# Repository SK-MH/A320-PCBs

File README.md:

# A320-PCBs

> [!IMPORTANT]
> This repository is still in progress.

Please wait for the documentation.
It could be found later on here.

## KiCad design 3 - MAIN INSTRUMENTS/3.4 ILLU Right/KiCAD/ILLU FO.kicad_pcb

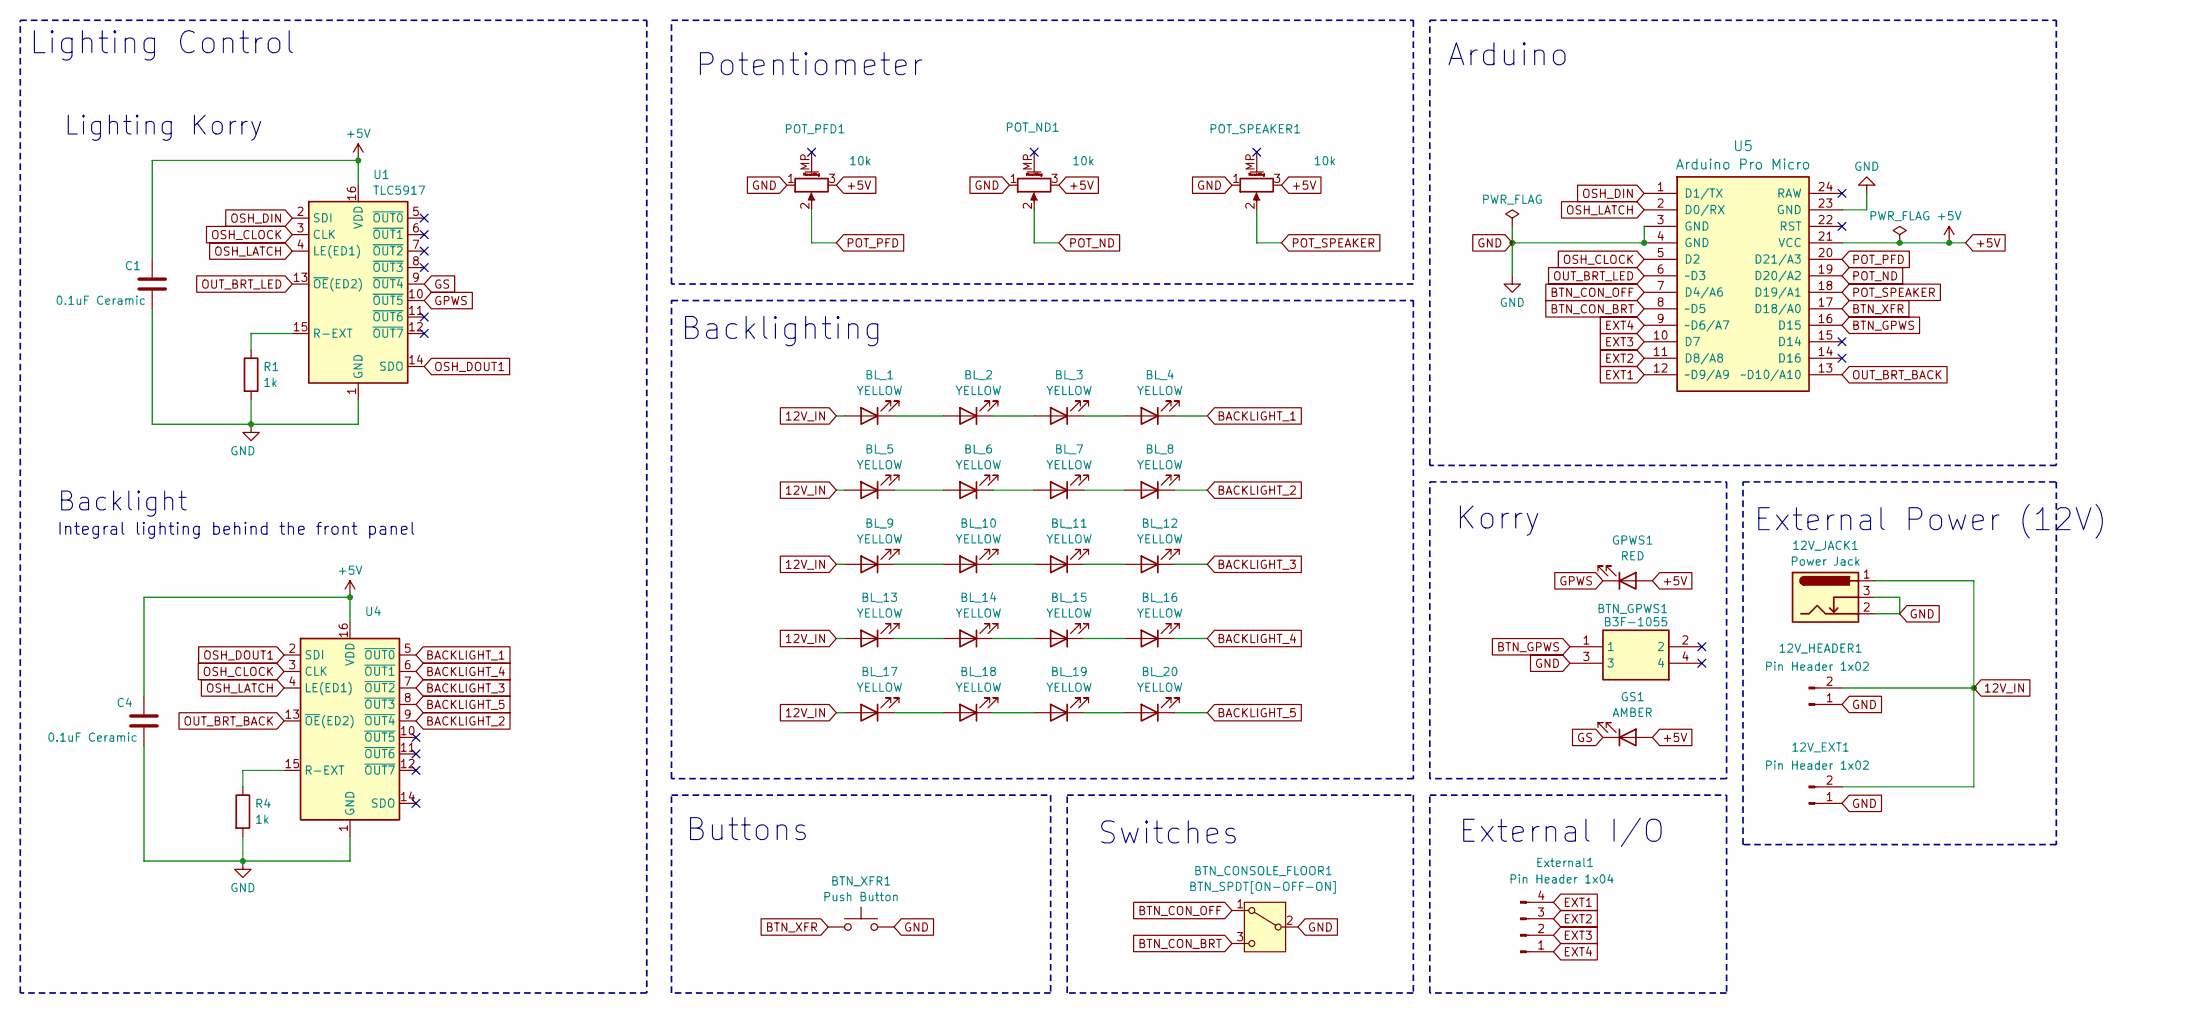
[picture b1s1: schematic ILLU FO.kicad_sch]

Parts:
12V_EXT1, 12V_HEADER1: Pin Header 1x02; JST_EH_B2B-EH-A_1x02_P2.50mm_Vertical
12V_JACK1: Power Jack; BarrelJack_Horizontal
BL_1, BL_2, BL_3, BL_4, BL_5, BL_6, BL_7, BL_8, BL_9, BL_10, BL_11, BL_12, BL_13, BL_14, BL_15, BL_16, BL_17, BL_18, BL_19, BL_20: YELLOW; LED_D3.0mm
BTN_CONSOLE_FLOOR1: BTN_SPDT[ON-OFF-ON]; T80-Z1
BTN_GPWS1: B3F-1055; B3F1000; Mouser Part Number 653-B3F-1055
BTN_XFR1: Push Button; SW-Push
C1, C4: 0.1uF Ceramic; C_Disc_D3.0mm_W1.6mm_P2.50mm
External1: Pin Header 1x04; JST_EH_B4B-EH-A_1x04_P2.50mm_Vertical
GPWS1: RED; LED_D3.0mm
GS1: AMBER; LED_D3.0mm
POT_ND1: 10k; Potentiometer_Alps_RK09K_Single_Vertical
POT_PFD1: 10k; Potentiometer_Alps_RK09K_Single_Vertical
POT_SPEAKER1: 10k; Potentiometer_Alps_RK09K_Single_Vertical
R1, R4: 1k; R_Axial_DIN0204_L3.6mm_D1.6mm_P7.62mm_Horizontal
U1, U4: TLC5917; DIP-16_W7.62mm
U5: Arduino Pro Micro; Sparkfun_Pro_Micro

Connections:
12V_IN: 12V_EXT1.2, 12V_HEADER1.2, 12V_JACK1.1, BL_1.2 (A), BL_5.2 (A), BL_9.2 (A), BL_13.2 (A), BL_17.2 (A)
+5V: C1.1, C4.1, GPWS1.2 (A), GS1.2 (A), POT_ND1.3, POT_PFD1.3, POT_SPEAKER1.3, U1.16 (VDD), U4.16 (VDD), U5.21 (VCC)
BACKLIGHT_1: BL_4.1 (K), U4.5 (~OUT0)
BACKLIGHT_2: BL_8.1 (K), U4.9 (~OUT4)
BACKLIGHT_3: BL_12.1 (K), U4.7 (~OUT2)
BACKLIGHT_4: BL_16.1 (K), U4.6 (~OUT1)
BACKLIGHT_5: BL_20.1 (K), U4.8 (~OUT3)
BTN_CON_BRT: BTN_CONSOLE_FLOOR1.3 (C), U5.8 (~D5)
BTN_CON_OFF: BTN_CONSOLE_FLOOR1.1 (A), U5.7 (D4/A6)
BTN_GPWS: BTN_GPWS1.1, U5.16 (D15)
BTN_XFR: BTN_XFR1.1, U5.17 (D18/A0)
EXT1: External1.4, U5.12 (~D9/A9)
EXT2: External1.3, U5.11 (D8/A8)
EXT3: External1.2, U5.10 (D7)
EXT4: External1.1, U5.9 (~D6/A7)
GND: 12V_EXT1.1, 12V_HEADER1.1, 12V_JACK1.2, 12V_JACK1.3, BTN_CONSOLE_FLOOR1.2 (B), BTN_GPWS1.3, BTN_XFR1.2, C1.2, C4.2, POT_ND1.1, POT_PFD1.1, POT_SPEAKER1.1, R1.2, R4.2, U1.1 (GND), U4.1 (GND), U5.3 (GND), U5.4 (GND), U5.23 (GND)
GPWS: GPWS1.1 (K), U1.10 (~OUT5)
GS: GS1.1 (K), U1.9 (~OUT4)
unnamed: BL_1.1 (K), BL_2.2 (A)
unnamed: BL_2.1 (K), BL_3.2 (A)
unnamed: BL_3.1 (K), BL_4.2 (A)
unnamed: BL_5.1 (K), BL_6.2 (A)
unnamed: BL_6.1 (K), BL_7.2 (A)
unnamed: BL_7.1 (K), BL_8.2 (A)
unnamed: BL_9.1 (K), BL_10.2 (A)
unnamed: BL_10.1 (K), BL_11.2 (A)
unnamed: BL_11.1 (K), BL_12.2 (A)
unnamed: BL_13.1 (K), BL_14.2 (A)
unnamed: BL_14.1 (K), BL_15.2 (A)
unnamed: BL_15.1 (K), BL_16.2 (A)
unnamed: BL_17.1 (K), BL_18.2 (A)
unnamed: BL_18.1 (K), BL_19.2 (A)
unnamed: BL_19.1 (K), BL_20.2 (A)
unnamed: R1.1, U1.15 (R-EXT)
unnamed: R4.1, U4.15 (R-EXT)
OSH_CLOCK: U1.3 (CLK), U4.3 (CLK), U5.5 (D2)
OSH_DIN: U1.2 (SDI), U5.1 (D1/TX)
OSH_DOUT1: U1.14 (SDO), U4.2 (SDI)
OSH_LATCH: U1.4 (LE(ED1)), U4.4 (LE(ED1)), U5.2 (D0/RX)
OUT_BRT_BACK: U4.13 (~OE(ED2)), U5.13 (~D10/A10)
OUT_BRT_LED: U1.13 (~OE(ED2)), U5.6 (~D3)
POT_ND: POT_ND1.2, U5.19 (D20/A2)
POT_PFD: POT_PFD1.2, U5.20 (D21/A3)
POT_SPEAKER: POT_SPEAKER1.2, U5.18 (D19/A1)

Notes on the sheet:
Backlighting
Arduino
Switches
External I/O
Korry
Buttons
External Power (12V)
Lighting Korry
Lighting Control
Integral lighting behind the front panel
Potentiometer
Backlight

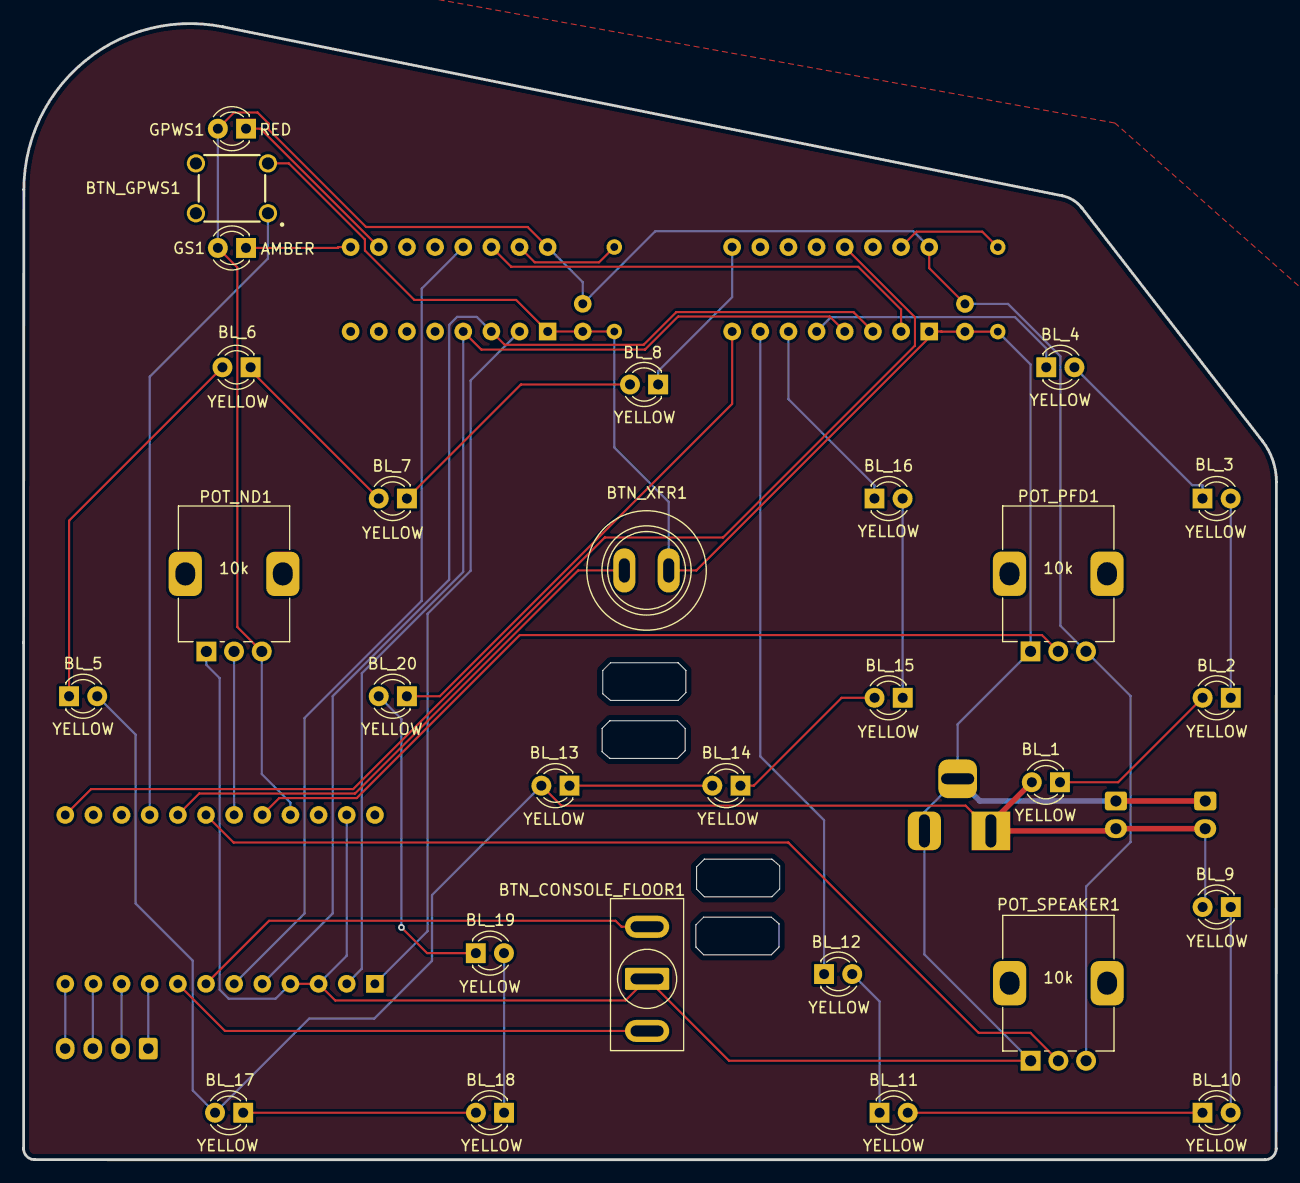
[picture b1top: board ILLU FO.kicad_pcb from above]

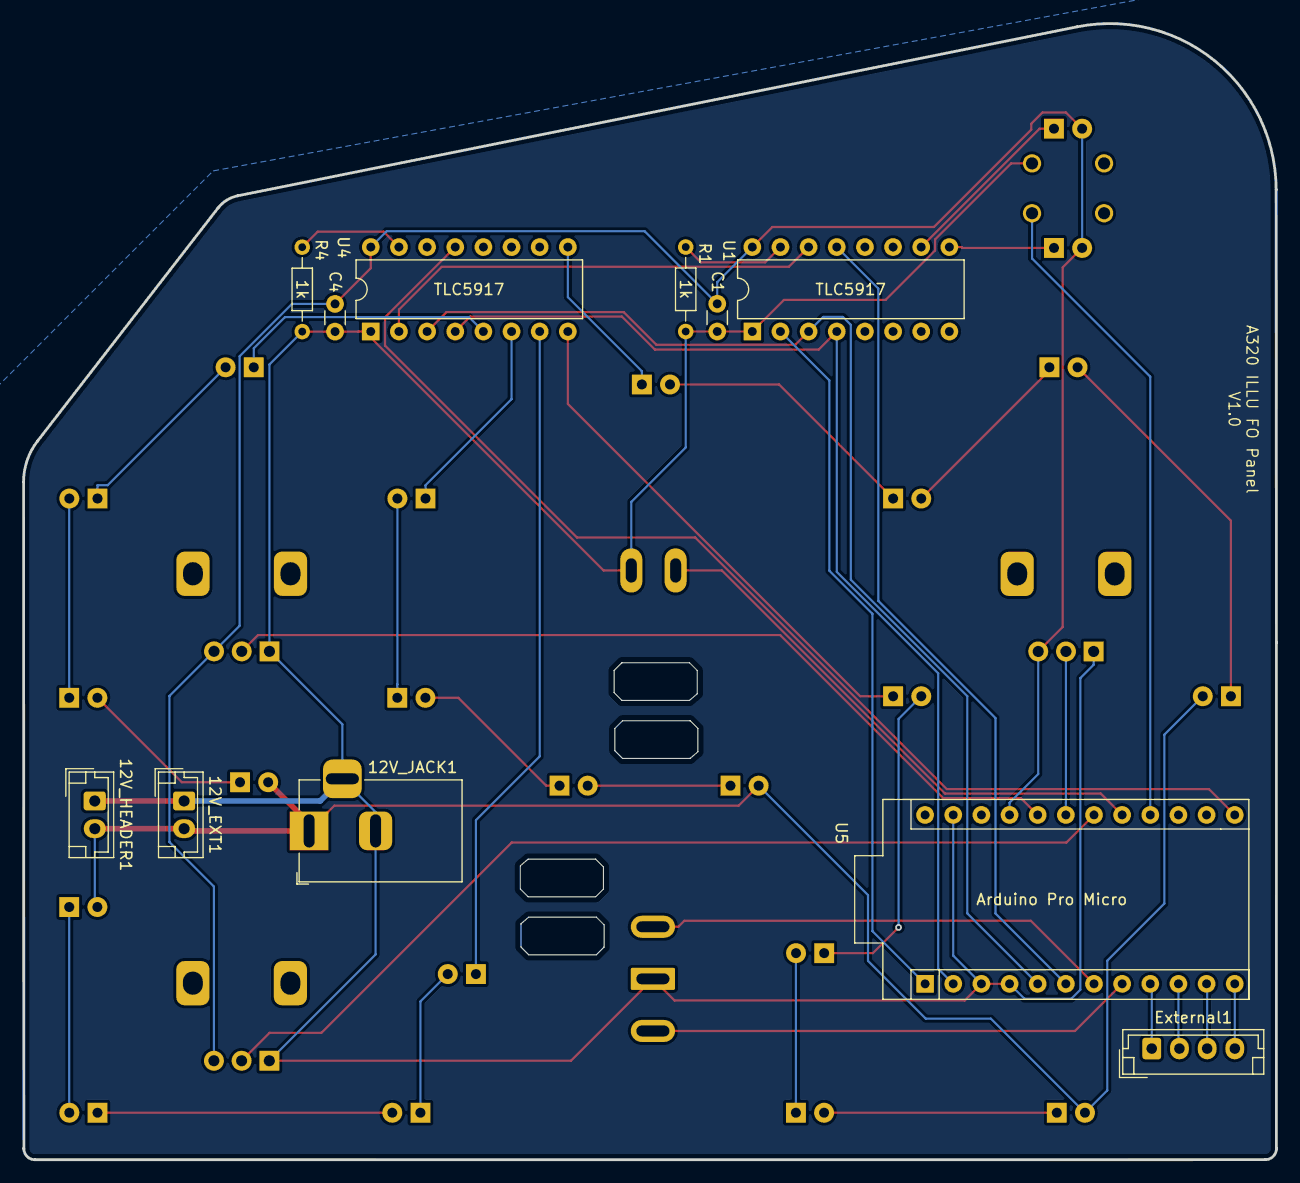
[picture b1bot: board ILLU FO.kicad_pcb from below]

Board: 2 copper layers, 113.0 x 102.5 mm, 39 parts (11 on the bottom side), 44 nets.

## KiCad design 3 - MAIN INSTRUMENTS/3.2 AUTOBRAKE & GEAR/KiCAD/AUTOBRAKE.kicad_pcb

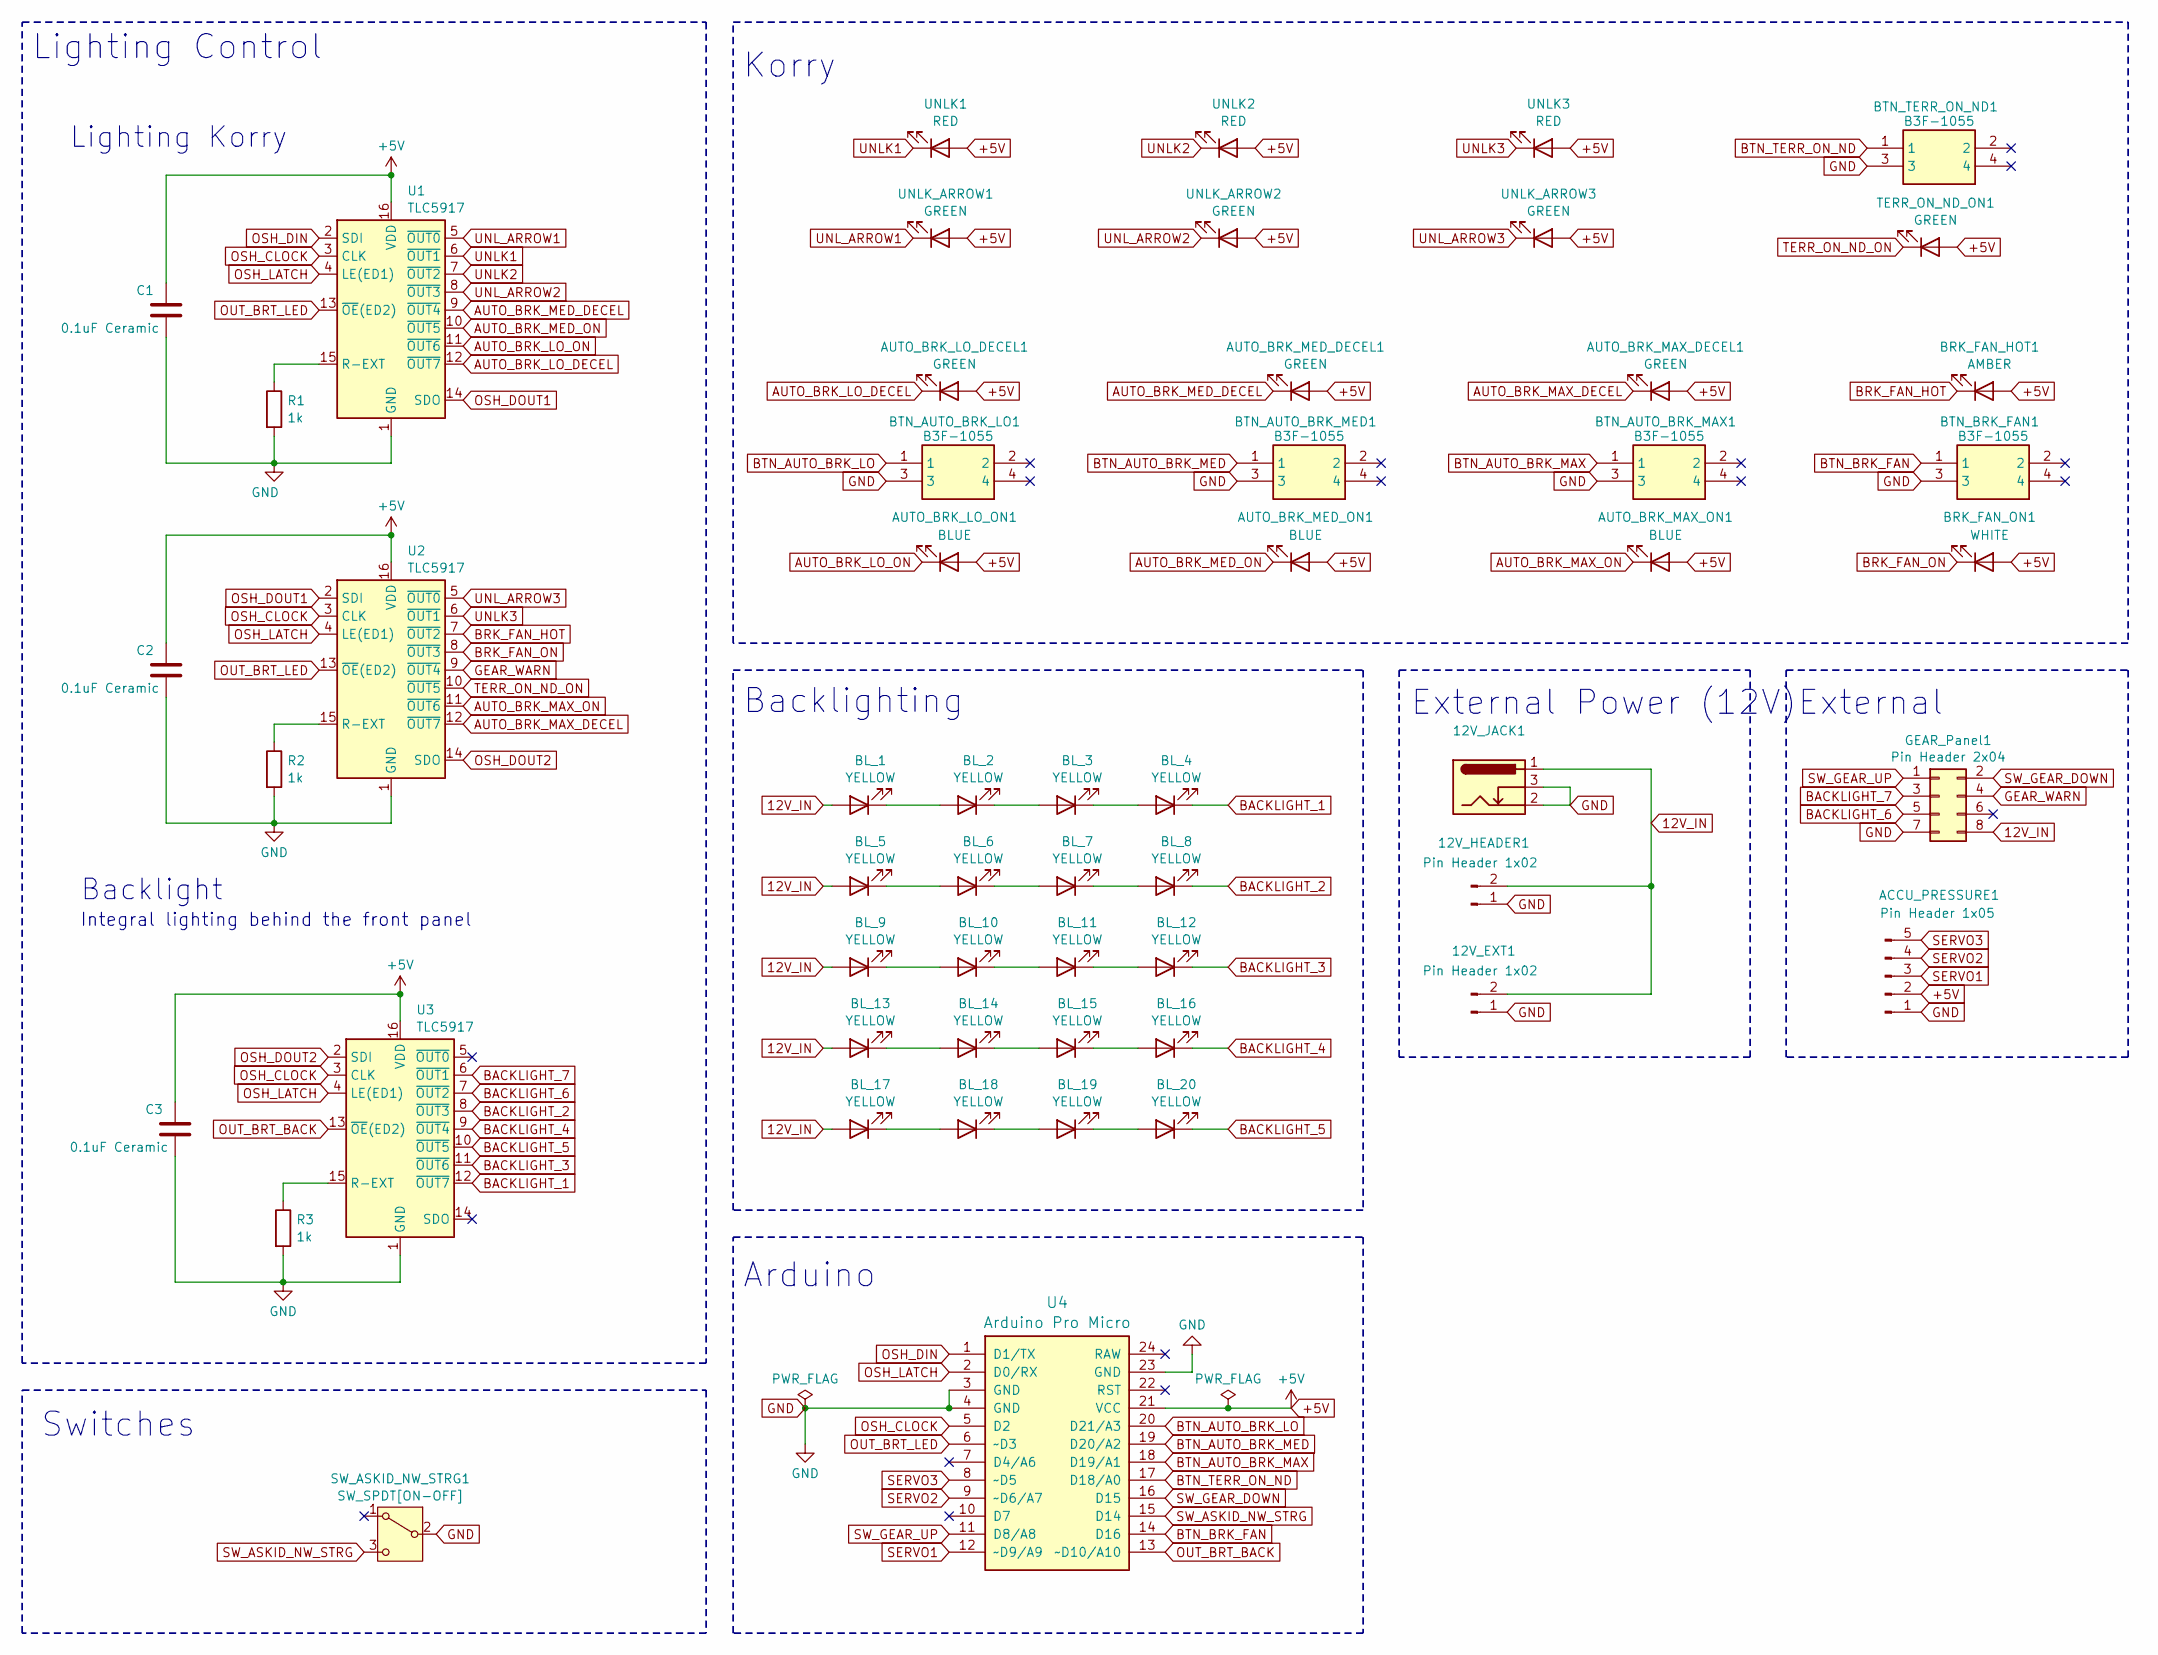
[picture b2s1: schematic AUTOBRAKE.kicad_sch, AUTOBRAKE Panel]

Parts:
12V_EXT1, 12V_HEADER1: Pin Header 1x02; JST_EH_B2B-EH-A_1x02_P2.50mm_Vertical
12V_JACK1: Power Jack; BarrelJack_Horizontal
ACCU_PRESSURE1: Pin Header 1x05; JST_EH_B5B-EH-A_1x05_P2.50mm_Vertical
AUTO_BRK_LO_DECEL1: GREEN; LED_D3.0mm
AUTO_BRK_LO_ON1: BLUE; LED_D3.0mm
AUTO_BRK_MAX_DECEL1: GREEN; LED_D3.0mm
AUTO_BRK_MAX_ON1: BLUE; LED_D3.0mm
AUTO_BRK_MED_DECEL1: GREEN; LED_D3.0mm
AUTO_BRK_MED_ON1: BLUE; LED_D3.0mm
BL_1, BL_2, BL_3, BL_4, BL_5, BL_6, BL_7, BL_8, BL_9, BL_10, BL_11, BL_12, BL_13, BL_14, BL_15, BL_16, BL_17, BL_18, BL_19, BL_20: YELLOW; LED_D3.0mm
BRK_FAN_HOT1: AMBER; LED_D3.0mm
BRK_FAN_ON1: WHITE; LED_D3.0mm
BTN_AUTO_BRK_LO1: B3F-1055; B3F1000; Mouser Part Number 653-B3F-1055
BTN_AUTO_BRK_MAX1: B3F-1055; B3F1000; Mouser Part Number 653-B3F-1055
BTN_AUTO_BRK_MED1: B3F-1055; B3F1000; Mouser Part Number 653-B3F-1055
BTN_BRK_FAN1: B3F-1055; B3F1000; Mouser Part Number 653-B3F-1055
BTN_TERR_ON_ND1: B3F-1055; B3F1000; Mouser Part Number 653-B3F-1055
C1, C2, C3: 0.1uF Ceramic; C_Disc_D3.0mm_W1.6mm_P2.50mm
GEAR_Panel1: Pin Header 2x04; IDC-Header_2x04_P2.54mm_Vertical
R1, R2, R3: 1k; R_Axial_DIN0204_L3.6mm_D1.6mm_P5.08mm_Horizontal
SW_ASKID_NW_STRG1: SW_SPDT[ON-OFF]; T80-Z1
TERR_ON_ND_ON1: GREEN; LED_D3.0mm
U1, U2, U3: TLC5917; DIP-16_W7.62mm
U4: Arduino Pro Micro; Sparkfun_Pro_Micro
UNLK1, UNLK2, UNLK3: RED; LED_D3.0mm
UNLK_ARROW1, UNLK_ARROW2, UNLK_ARROW3: GREEN; LED_D3.0mm

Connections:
12V_IN: 12V_EXT1.2, 12V_HEADER1.2, 12V_JACK1.1, BL_1.2 (A), BL_5.2 (A), BL_9.2 (A), BL_13.2 (A), BL_17.2 (A), GEAR_Panel1.8
+5V: ACCU_PRESSURE1.2, AUTO_BRK_LO_DECEL1.2 (A), AUTO_BRK_LO_ON1.2 (A), AUTO_BRK_MAX_DECEL1.2 (A), AUTO_BRK_MAX_ON1.2 (A), AUTO_BRK_MED_DECEL1.2 (A), AUTO_BRK_MED_ON1.2 (A), BRK_FAN_HOT1.2 (A), BRK_FAN_ON1.2 (A), C1.1, C2.1, C3.1, TERR_ON_ND_ON1.2 (A), U1.16 (VDD), U2.16 (VDD), U3.16 (VDD), U4.21 (VCC), UNLK1.2 (A), UNLK2.2 (A), UNLK3.2 (A), UNLK_ARROW1.2 (A), UNLK_ARROW2.2 (A), UNLK_ARROW3.2 (A)
AUTO_BRK_LO_DECEL: AUTO_BRK_LO_DECEL1.1 (K), U1.12 (~OUT7)
AUTO_BRK_LO_ON: AUTO_BRK_LO_ON1.1 (K), U1.11 (~OUT6)
AUTO_BRK_MAX_DECEL: AUTO_BRK_MAX_DECEL1.1 (K), U2.12 (~OUT7)
AUTO_BRK_MAX_ON: AUTO_BRK_MAX_ON1.1 (K), U2.11 (~OUT6)
AUTO_BRK_MED_DECEL: AUTO_BRK_MED_DECEL1.1 (K), U1.9 (~OUT4)
AUTO_BRK_MED_ON: AUTO_BRK_MED_ON1.1 (K), U1.10 (~OUT5)
BACKLIGHT_1: BL_4.1 (K), U3.12 (~OUT7)
BACKLIGHT_2: BL_8.1 (K), U3.8 (~OUT3)
BACKLIGHT_3: BL_12.1 (K), U3.11 (~OUT6)
BACKLIGHT_4: BL_16.1 (K), U3.9 (~OUT4)
BACKLIGHT_5: BL_20.1 (K), U3.10 (~OUT5)
BACKLIGHT_6: GEAR_Panel1.5, U3.7 (~OUT2)
BACKLIGHT_7: GEAR_Panel1.3, U3.6 (~OUT1)
BRK_FAN_HOT: BRK_FAN_HOT1.1 (K), U2.7 (~OUT2)
BRK_FAN_ON: BRK_FAN_ON1.1 (K), U2.8 (~OUT3)
BTN_AUTO_BRK_LO: BTN_AUTO_BRK_LO1.1, U4.20 (D21/A3)
BTN_AUTO_BRK_MAX: BTN_AUTO_BRK_MAX1.1, U4.18 (D19/A1)
BTN_AUTO_BRK_MED: BTN_AUTO_BRK_MED1.1, U4.19 (D20/A2)
BTN_BRK_FAN: BTN_BRK_FAN1.1, U4.14 (D16)
BTN_TERR_ON_ND: BTN_TERR_ON_ND1.1, U4.17 (D18/A0)
GEAR_WARN: GEAR_Panel1.4, U2.9 (~OUT4)
GND: 12V_EXT1.1, 12V_HEADER1.1, 12V_JACK1.2, 12V_JACK1.3, ACCU_PRESSURE1.1, BTN_AUTO_BRK_LO1.3, BTN_AUTO_BRK_MAX1.3, BTN_AUTO_BRK_MED1.3, BTN_BRK_FAN1.3, BTN_TERR_ON_ND1.3, C1.2, C2.2, C3.2, GEAR_Panel1.7, R1.2, R2.2, R3.2, SW_ASKID_NW_STRG1.2 (B), U1.1 (GND), U2.1 (GND), U3.1 (GND), U4.3 (GND), U4.4 (GND), U4.23 (GND)
unnamed: BL_1.1 (K), BL_2.2 (A)
unnamed: BL_2.1 (K), BL_3.2 (A)
unnamed: BL_3.1 (K), BL_4.2 (A)
unnamed: BL_5.1 (K), BL_6.2 (A)
unnamed: BL_6.1 (K), BL_7.2 (A)
unnamed: BL_7.1 (K), BL_8.2 (A)
unnamed: BL_9.1 (K), BL_10.2 (A)
unnamed: BL_10.1 (K), BL_11.2 (A)
unnamed: BL_11.1 (K), BL_12.2 (A)
unnamed: BL_13.1 (K), BL_14.2 (A)
unnamed: BL_14.1 (K), BL_15.2 (A)
unnamed: BL_15.1 (K), BL_16.2 (A)
unnamed: BL_17.1 (K), BL_18.2 (A)
unnamed: BL_18.1 (K), BL_19.2 (A)
unnamed: BL_19.1 (K), BL_20.2 (A)
unnamed: R1.1, U1.15 (R-EXT)
unnamed: R2.1, U2.15 (R-EXT)
unnamed: R3.1, U3.15 (R-EXT)
OSH_CLOCK: U1.3 (CLK), U2.3 (CLK), U3.3 (CLK), U4.5 (D2)
OSH_DIN: U1.2 (SDI), U4.1 (D1/TX)
OSH_DOUT1: U1.14 (SDO), U2.2 (SDI)
OSH_DOUT2: U2.14 (SDO), U3.2 (SDI)
OSH_LATCH: U1.4 (LE(ED1)), U2.4 (LE(ED1)), U3.4 (LE(ED1)), U4.2 (D0/RX)
OUT_BRT_BACK: U3.13 (~OE(ED2)), U4.13 (~D10/A10)
OUT_BRT_LED: U1.13 (~OE(ED2)), U2.13 (~OE(ED2)), U4.6 (~D3)
SERVO1: ACCU_PRESSURE1.3, U4.12 (~D9/A9)
SERVO2: ACCU_PRESSURE1.4, U4.9 (~D6/A7)
SERVO3: ACCU_PRESSURE1.5, U4.8 (~D5)
SW_ASKID_NW_STRG: SW_ASKID_NW_STRG1.3 (C), U4.15 (D14)
SW_GEAR_DOWN: GEAR_Panel1.2, U4.16 (D15)
SW_GEAR_UP: GEAR_Panel1.1, U4.11 (D8/A8)
TERR_ON_ND_ON: TERR_ON_ND_ON1.1 (K), U2.10 (~OUT5)
UNLK1: U1.6 (~OUT1), UNLK1.1 (K)
UNLK2: U1.7 (~OUT2), UNLK2.1 (K)
UNLK3: U2.6 (~OUT1), UNLK3.1 (K)
UNL_ARROW1: U1.5 (~OUT0), UNLK_ARROW1.1 (K)
UNL_ARROW2: U1.8 (~OUT3), UNLK_ARROW2.1 (K)
UNL_ARROW3: U2.5 (~OUT0), UNLK_ARROW3.1 (K)

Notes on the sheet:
Backlighting
Arduino
Switches
Korry
External Power (12V)
Lighting Korry
Lighting Control
Integral lighting behind the front panel
Backlight
External

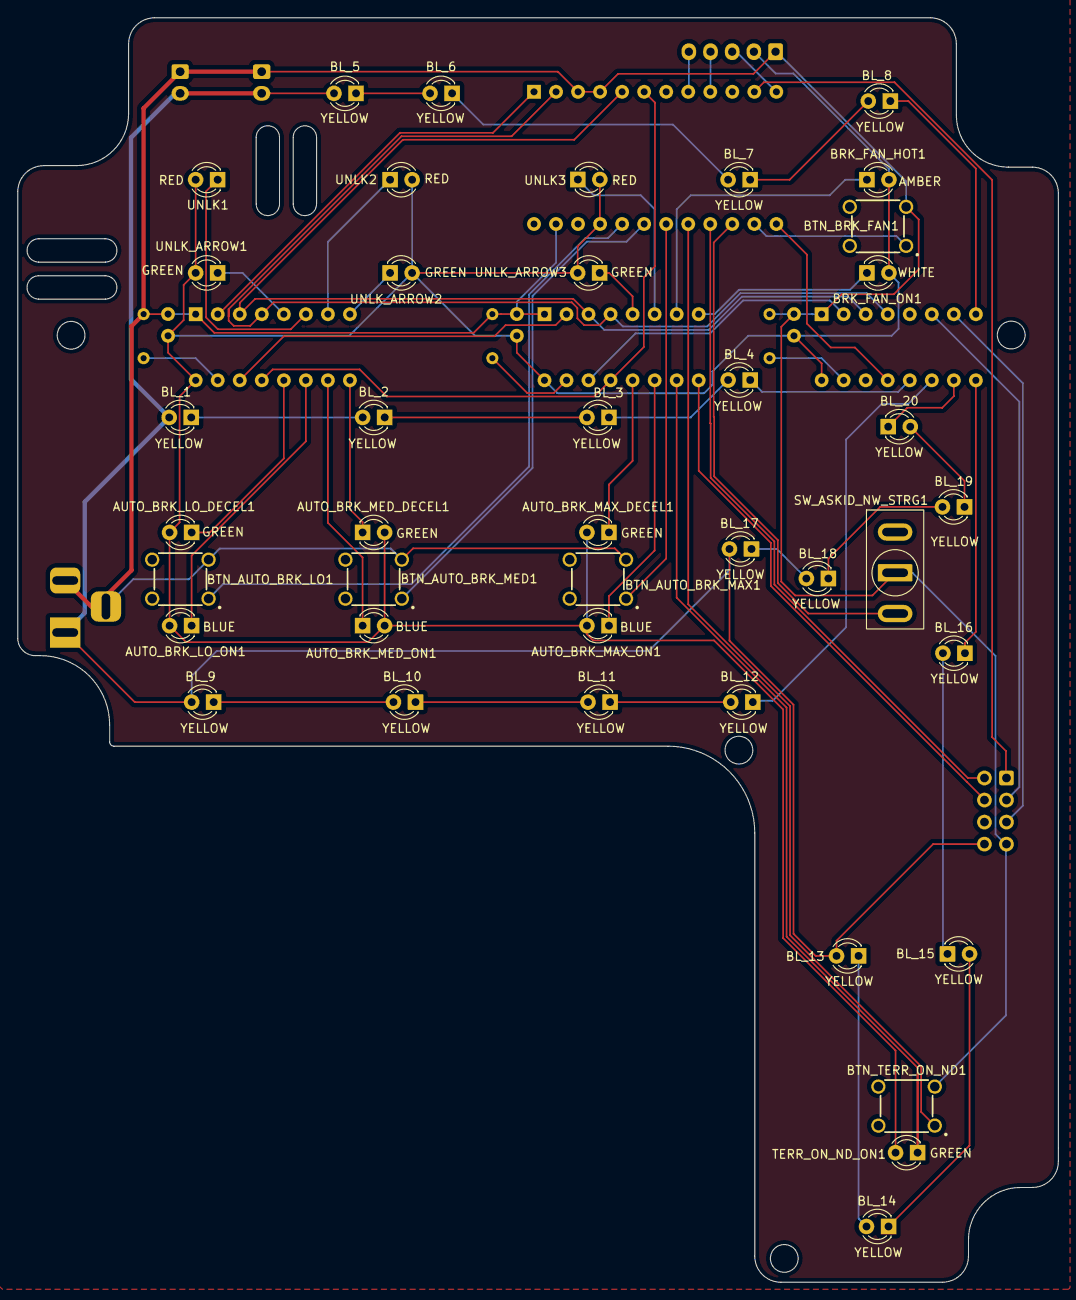
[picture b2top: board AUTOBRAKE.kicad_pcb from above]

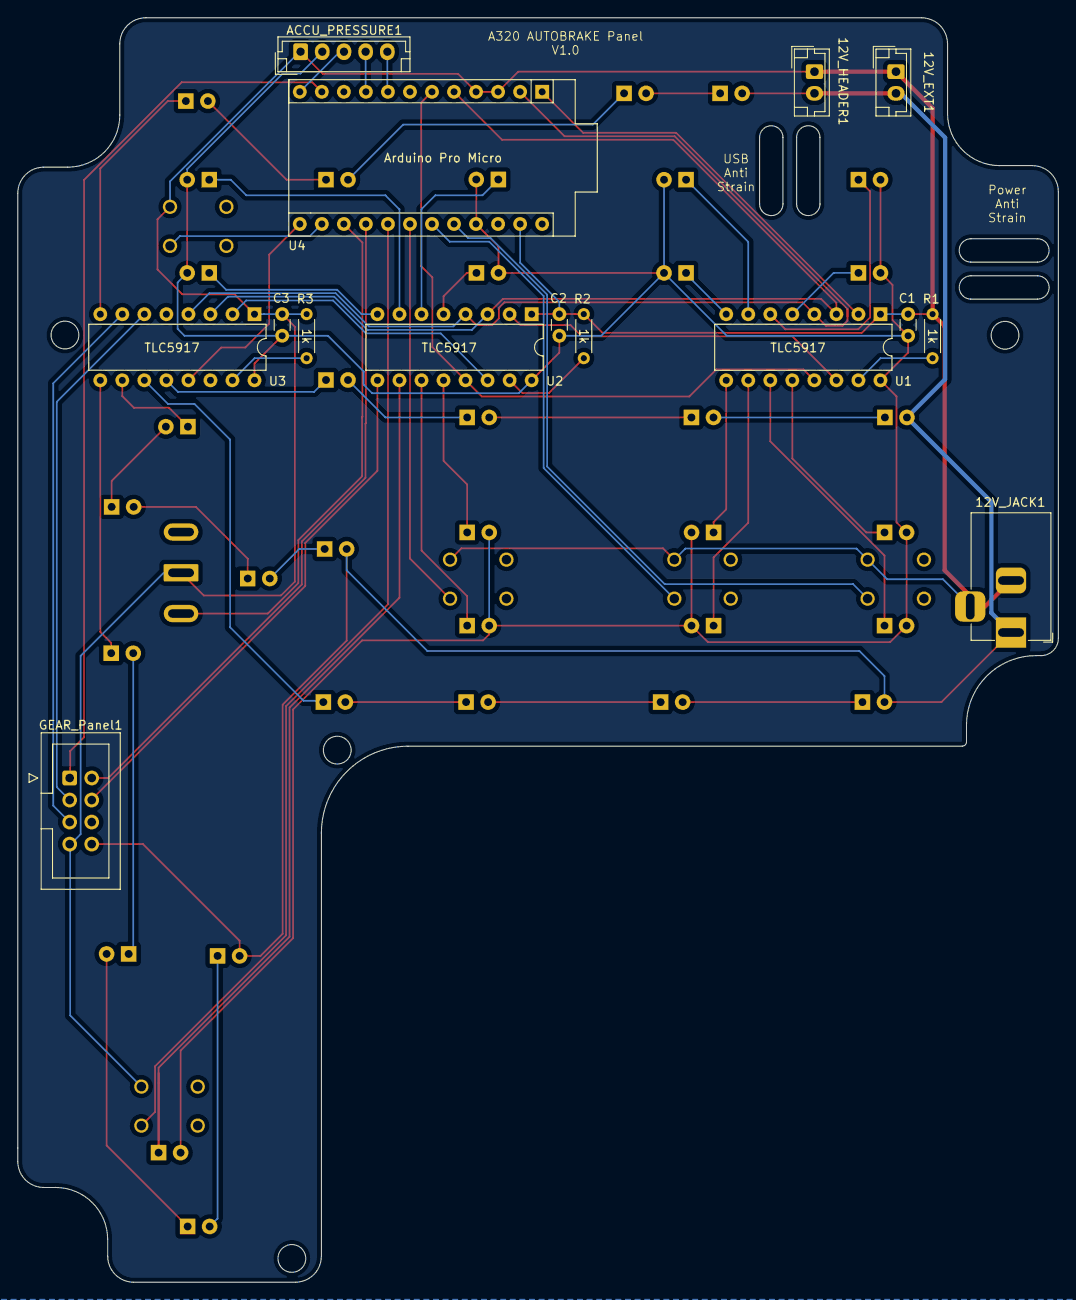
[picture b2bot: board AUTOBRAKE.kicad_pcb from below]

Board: 2 copper layers, 120.0 x 145.8 mm, 56 parts (15 on the bottom side), 62 nets.
